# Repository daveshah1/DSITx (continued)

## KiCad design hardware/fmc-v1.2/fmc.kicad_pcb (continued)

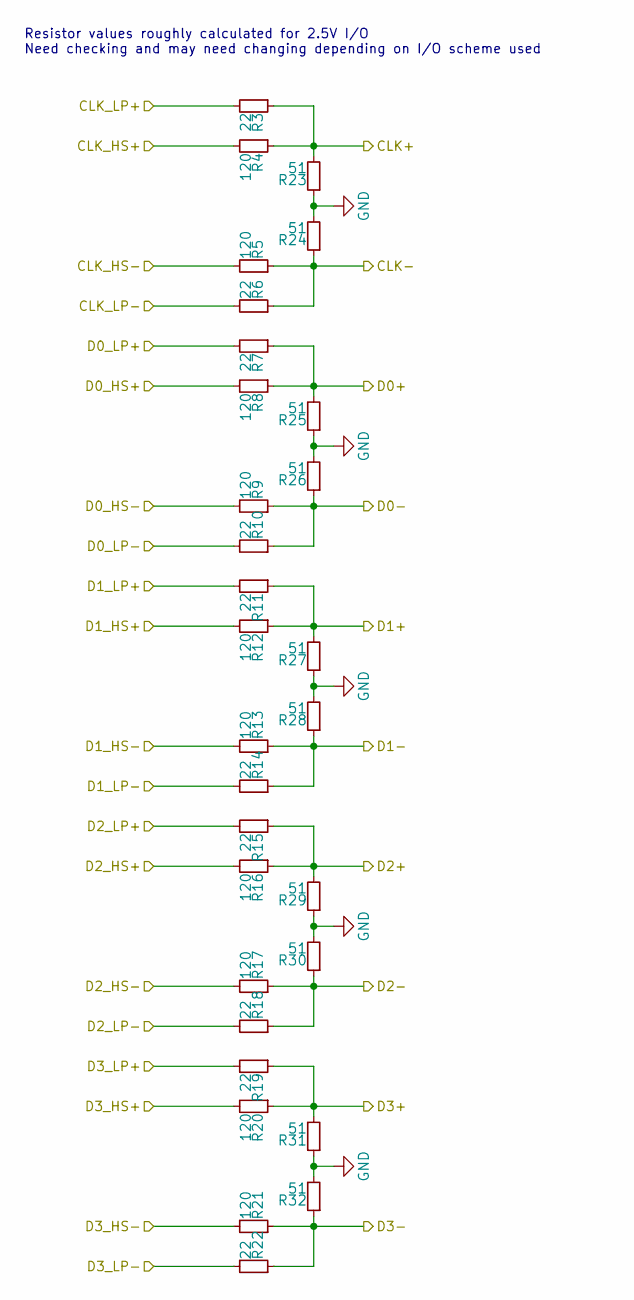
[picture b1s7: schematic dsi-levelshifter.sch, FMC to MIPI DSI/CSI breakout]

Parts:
R3, R6, R7, R10, R11, R14, R15, R18, R19, R22: 22; R_0402
R4, R5, R8, R9, R12, R13, R16, R17, R20, R21: 120; R_0402
R23, R24, R25, R26, R27, R28, R29, R30, R31, R32: 51; R_0402

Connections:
DSI0_CLK+: R3.1, R4.1, R23.2; also elsewhere on the board
DSI0_CLK-: R5.1, R6.1, R24.1; also elsewhere on the board
DSI0_CLK_HS+: R4.2; also elsewhere on the board
DSI0_CLK_HS-: R5.2; also elsewhere on the board
DSI0_CLK_LP+: R3.2; also elsewhere on the board
DSI0_CLK_LP-: R6.2; also elsewhere on the board
DSI0_D0+: R7.1, R8.1, R25.2; also elsewhere on the board
DSI0_D0-: R9.1, R10.1, R26.1; also elsewhere on the board
DSI0_D0_HS+: R8.2; also elsewhere on the board
DSI0_D0_HS-: R9.2; also elsewhere on the board
DSI0_D0_LP+: R7.2; also elsewhere on the board
DSI0_D0_LP-: R10.2; also elsewhere on the board
DSI0_D1+: R11.1, R12.1, R27.2; also elsewhere on the board
DSI0_D1-: R13.1, R14.1, R28.1; also elsewhere on the board
DSI0_D1_HS+: R12.2; also elsewhere on the board
DSI0_D1_HS-: R13.2; also elsewhere on the board
DSI0_D1_LP+: R11.2; also elsewhere on the board
DSI0_D1_LP-: R14.2; also elsewhere on the board
DSI0_D2+: R15.1, R16.1, R29.2; also elsewhere on the board
DSI0_D2-: R17.1, R18.1, R30.1; also elsewhere on the board
DSI0_D2_HS+: R16.2; also elsewhere on the board
DSI0_D2_HS-: R17.2; also elsewhere on the board
DSI0_D2_LP+: R15.2; also elsewhere on the board
DSI0_D2_LP-: R18.2; also elsewhere on the board
DSI0_D3+: R19.1, R20.1, R31.2; also elsewhere on the board
DSI0_D3-: R21.1, R22.1, R32.1; also elsewhere on the board
DSI0_D3_HS+: R20.2; also elsewhere on the board
DSI0_D3_HS-: R21.2; also elsewhere on the board
DSI0_D3_LP+: R19.2; also elsewhere on the board
DSI0_D3_LP-: R22.2; also elsewhere on the board
GND: R23.1, R24.2, R25.1, R26.2, R27.1, R28.2, R29.1, R30.2, R31.1, R32.2; also elsewhere on the board

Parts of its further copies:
R33, R36, R37, R40, R41, R44, R45, R48, R49, R52: 22; R_0402
R34, R35, R38, R39, R42, R43, R46, R47, R50, R51: 120; R_0402
R53, R54, R55, R56, R57, R58, R59, R60, R61, R62: 51; R_0402

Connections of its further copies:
DSI1_CLK+: R33.1, R34.1, R53.2; also elsewhere on the board
DSI1_CLK-: R35.1, R36.1, R54.1; also elsewhere on the board
DSI1_CLK_HS+: R34.2; also elsewhere on the board
DSI1_CLK_HS-: R35.2; also elsewhere on the board
DSI1_CLK_LP+: R33.2; also elsewhere on the board
DSI1_CLK_LP-: R36.2; also elsewhere on the board
DSI1_D0+: R37.1, R38.1, R55.2; also elsewhere on the board
DSI1_D0-: R39.1, R40.1, R56.1; also elsewhere on the board
DSI1_D0_HS+: R38.2; also elsewhere on the board
DSI1_D0_HS-: R39.2; also elsewhere on the board
DSI1_D0_LP+: R37.2; also elsewhere on the board
DSI1_D0_LP-: R40.2; also elsewhere on the board
DSI1_D1+: R41.1, R42.1, R57.2; also elsewhere on the board
DSI1_D1-: R43.1, R44.1, R58.1; also elsewhere on the board
DSI1_D1_HS+: R42.2; also elsewhere on the board
DSI1_D1_HS-: R43.2; also elsewhere on the board
DSI1_D1_LP+: R41.2; also elsewhere on the board
DSI1_D1_LP-: R44.2; also elsewhere on the board
DSI1_D2+: R45.1, R46.1, R59.2; also elsewhere on the board
DSI1_D2-: R47.1, R48.1, R60.1; also elsewhere on the board
DSI1_D2_HS+: R46.2; also elsewhere on the board
DSI1_D2_HS-: R47.2; also elsewhere on the board
DSI1_D2_LP+: R45.2; also elsewhere on the board
DSI1_D2_LP-: R48.2; also elsewhere on the board
DSI1_D3+: R49.1, R50.1, R61.2; also elsewhere on the board
DSI1_D3-: R51.1, R52.1, R62.1; also elsewhere on the board
DSI1_D3_HS+: R50.2; also elsewhere on the board
DSI1_D3_HS-: R51.2; also elsewhere on the board
DSI1_D3_LP+: R49.2; also elsewhere on the board
DSI1_D3_LP-: R52.2; also elsewhere on the board
GND: R53.1, R54.2, R55.1, R56.2, R57.1, R58.2, R59.1, R60.2, R61.1, R62.2; also elsewhere on the board

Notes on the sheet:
Resistor values roughly calculated for 2.5V I/O Need checking and may need changing depending on I/O scheme used

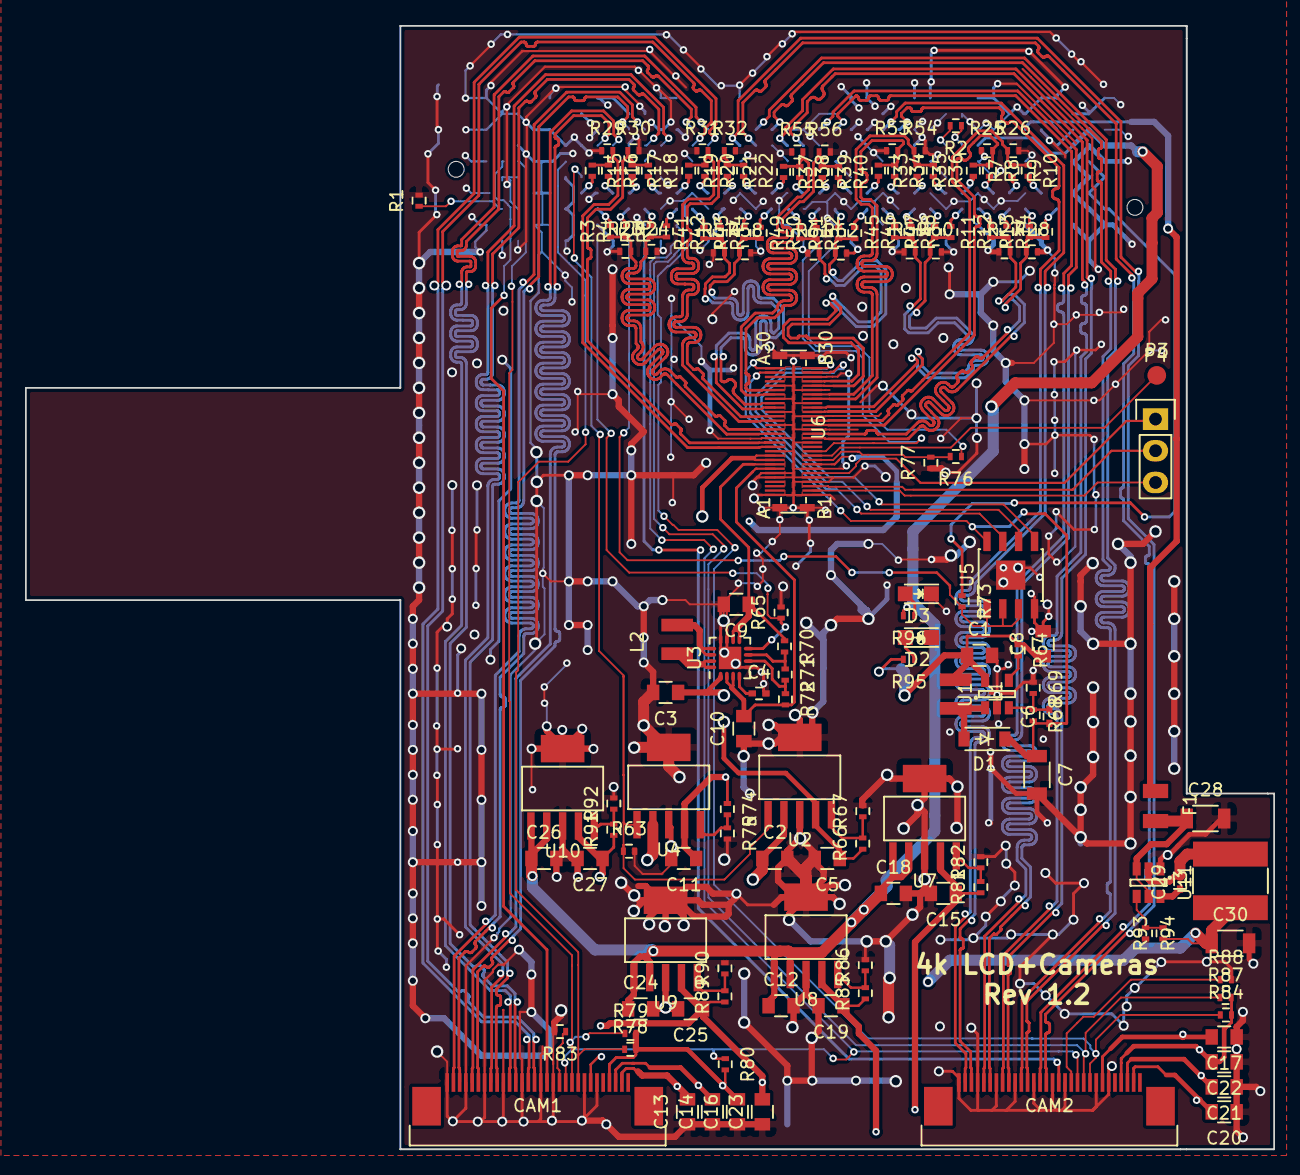
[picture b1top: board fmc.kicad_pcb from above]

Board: 4 copper layers, 100.0 x 90.0 mm, 149 parts (1 on the bottom side), 139 nets.

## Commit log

2017-04-25 Initial code and hardware commit
